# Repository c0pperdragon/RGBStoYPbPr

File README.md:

# RGBStoYPbPr

A fairly simple video converter from RGBS to YPbPr. My main challenge here is to make it work with only stuff that I have incidentially at home.
 
The PCB is a small single-sided leftover piece that was just big enough to fit the circuitry. Home etching, using the well-known toner transfer method,
turned out pretty nicely. To create the necessary non-standard resistor values, I soldered several resistors on top of each other. 
When allowing up to three resistors in a parallel configuration, the computer search finds an extremly good fit for every desired value
by using only the E6 series.

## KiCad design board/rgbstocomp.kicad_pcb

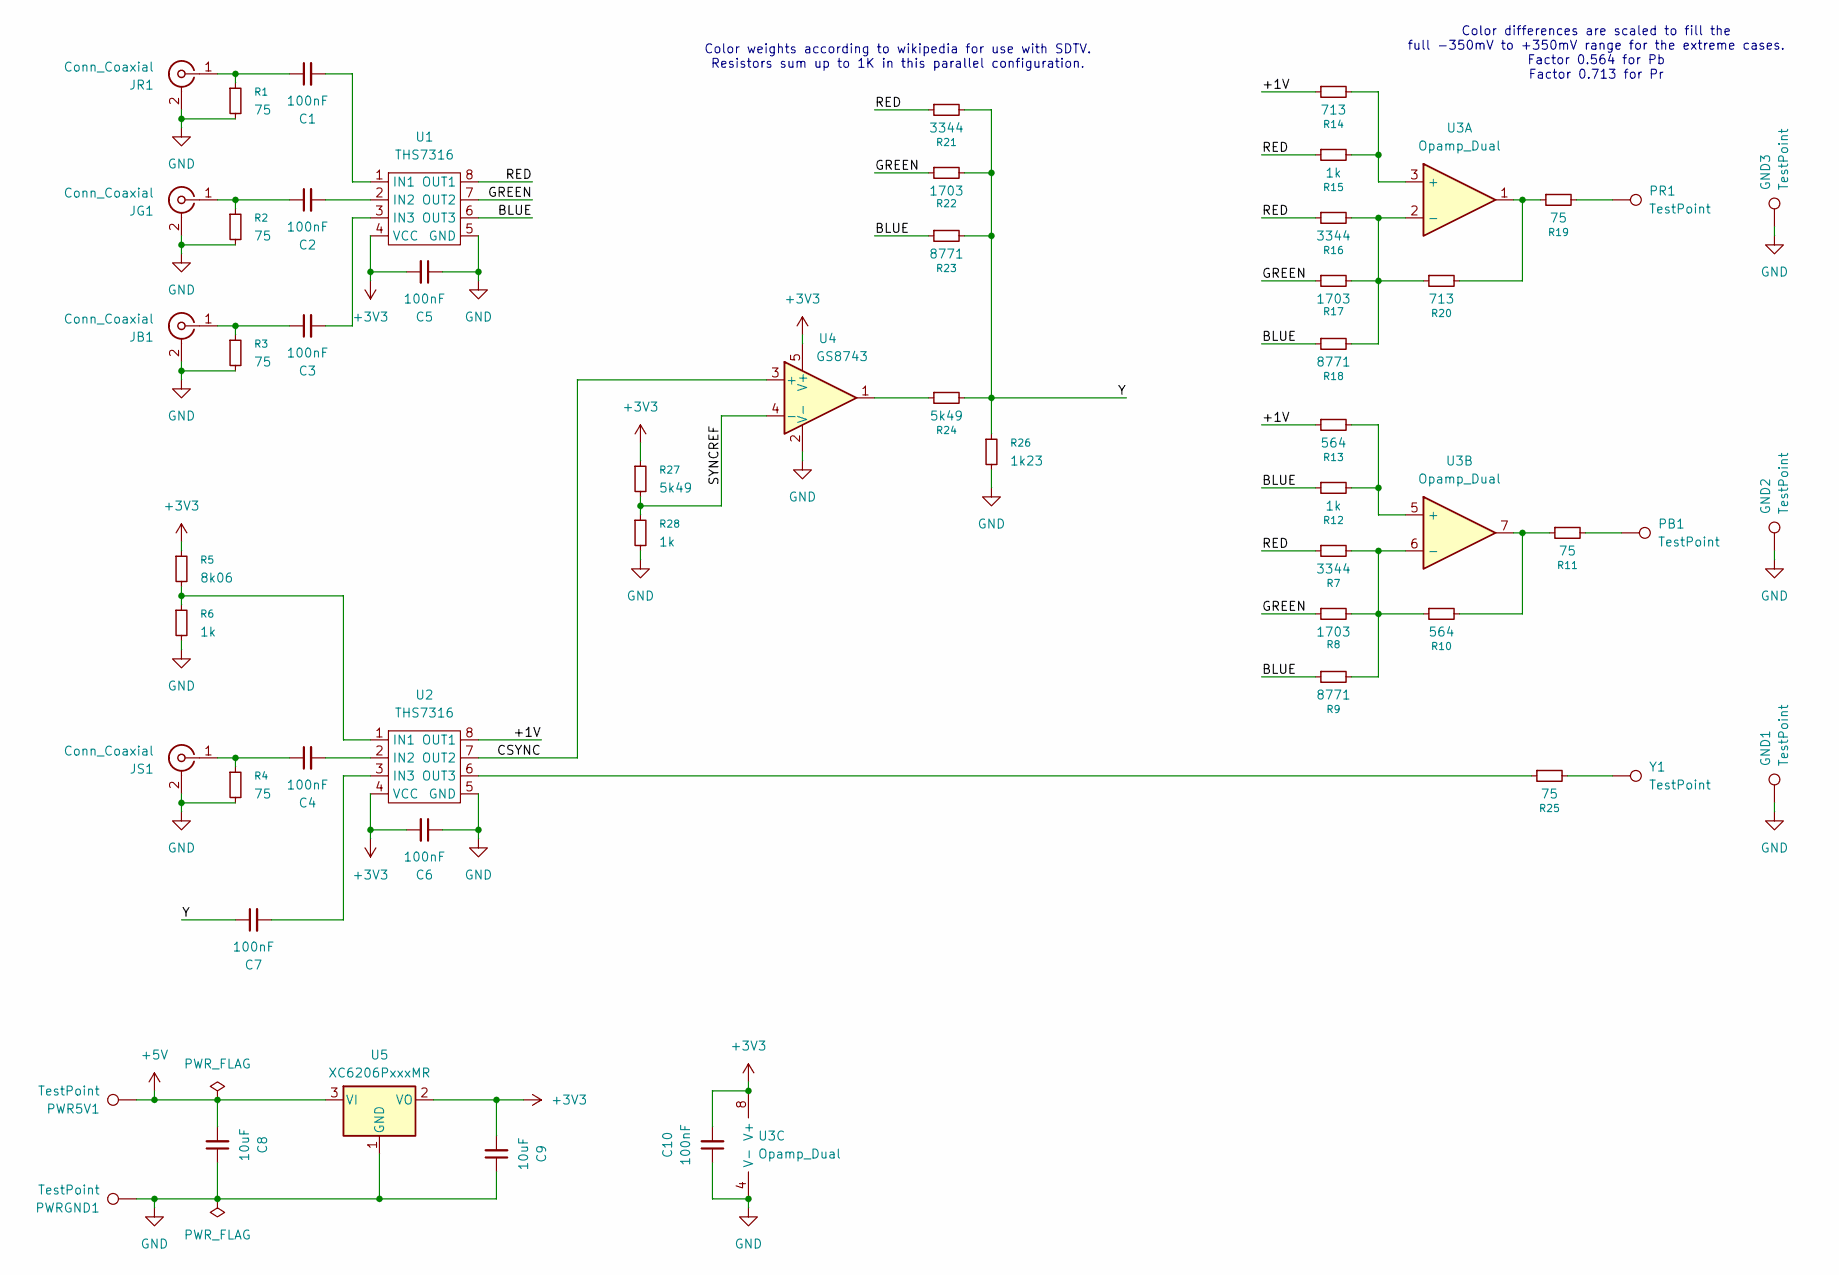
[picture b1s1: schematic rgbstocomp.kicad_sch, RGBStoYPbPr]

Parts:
C1, C2, C3, C4, C5, C6, C7, C10: 100nF; C_0805_2012Metric_Pad1.18x1.45mm_HandSolder
C8, C9: 10uF; C_0805_2012Metric_Pad1.18x1.45mm_HandSolder
GND1, GND2, GND3: TestPoint; TestPoint_Pad_3.0x3.0mm
JB1: Conn_Coaxial; 156-0097-E
JG1: Conn_Coaxial; 156-0097-E
JR1: Conn_Coaxial; 156-0097-E
JS1: Conn_Coaxial; 156-0097-E
PB1: TestPoint; TestPoint_Pad_3.0x3.0mm
PR1: TestPoint; TestPoint_Pad_3.0x3.0mm
PWR5V1: TestPoint; TestPoint_Pad_3.0x3.0mm
PWRGND1: TestPoint; TestPoint_Pad_3.0x3.0mm
R1, R2, R3, R4, R11, R19, R25: 75; R_0805_2012Metric_Pad1.20x1.40mm_HandSolder
R5: 8k06; R_0805_2012Metric_Pad1.20x1.40mm_HandSolder
R6, R12, R15, R28: 1k; R_0805_2012Metric_Pad1.20x1.40mm_HandSolder
R7, R16, R21: 3344; R_0805_2012Metric_Pad1.20x1.40mm_HandSolder
R8, R17, R22: 1703; R_0805_2012Metric_Pad1.20x1.40mm_HandSolder
R9, R18, R23: 8771; R_0805_2012Metric_Pad1.20x1.40mm_HandSolder
R10, R13: 564; R_0805_2012Metric_Pad1.20x1.40mm_HandSolder
R14, R20: 713; R_0805_2012Metric_Pad1.20x1.40mm_HandSolder
R24, R27: 5k49; R_0805_2012Metric_Pad1.20x1.40mm_HandSolder
R26: 1k23; R_0805_2012Metric_Pad1.20x1.40mm_HandSolder
U1, U2: THS7316; SO-8_3.9x4.9mm_P1.27mm
U3: Opamp_Dual; SO-8_3.9x4.9mm_P1.27mm
U4: GS8743; SOT-23-5
U5: XC6206PxxxMR; SOT-23-3
Y1: TestPoint; TestPoint_Pad_3.0x3.0mm

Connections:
+3V3: C5.2, C6.2, C9.2, C10.2, R5.1, R27.1, U1.4 (VCC), U2.4 (VCC), U3.8 (V+), U4.5 (V+), U5.2 (VO)
+5V: C8.2, PWR5V1.1, U5.3 (VI)
/+1V: R13.1, R14.1, U2.8 (OUT1)
/BLUE: R9.1, R12.1, R18.1, R23.1, U1.6 (OUT3)
/CSYNC: U2.7 (OUT2), U4.3 (+)
/GREEN: R8.1, R17.1, R22.1, U1.7 (OUT2)
/RED: R7.1, R15.1, R16.1, R21.1, U1.8 (OUT1)
/SYNCREF: R27.2, R28.1, U4.4 (-)
/Y: C7.1, R21.2, R22.2, R23.2, R24.2, R26.1
GND: C5.1, C6.1, C8.1, C9.1, C10.1, GND1.1, GND2.1, GND3.1, JB1.2 (Ext), JG1.2 (Ext), JR1.2 (Ext), JS1.2 (Ext), PWRGND1.1, R1.2, R2.2, R3.2, R4.2, R6.2, R26.2, R28.2, U1.5 (GND), U2.5 (GND), U3.4 (V-), U4.2 (V-), U5.1 (GND)
unnamed: C3.1, JB1.1 (In), R3.1
unnamed: C2.1, JG1.1 (In), R2.1
unnamed: C1.1, JR1.1 (In), R1.1
unnamed: C4.1, JS1.1 (In), R4.1
unnamed: PB1.1, R11.2
unnamed: PR1.1, R19.2
unnamed: R10.2, R11.1, U3.7
unnamed: R19.1, R20.2, U3.1
unnamed: R24.1, U4.1
unnamed: R25.2, Y1.1
unnamed: C1.2, U1.1 (IN1)
unnamed: C2.2, U1.2 (IN2)
unnamed: C3.2, U1.3 (IN3)
unnamed: R5.2, R6.1, U2.1 (IN1)
unnamed: C4.2, U2.2 (IN2)
unnamed: C7.2, U2.3 (IN3)
unnamed: R25.1, U2.6 (OUT3)
unnamed: R14.2, R15.2, U3.3 (+)
unnamed: R16.2, R17.2, R18.2, R20.1, U3.2 (-)
unnamed: R12.2, R13.2, U3.5 (+)
unnamed: R7.2, R8.2, R9.2, R10.1, U3.6 (-)

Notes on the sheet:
Color differences are scaled to fill the full -350mV to +350mV range for the extreme cases. Factor 0.564 for Pb Factor 0.713 for Pr
Color weights according to wikipedia for use with SDTV. Resistors sum up to 1K in this parallel configuration.

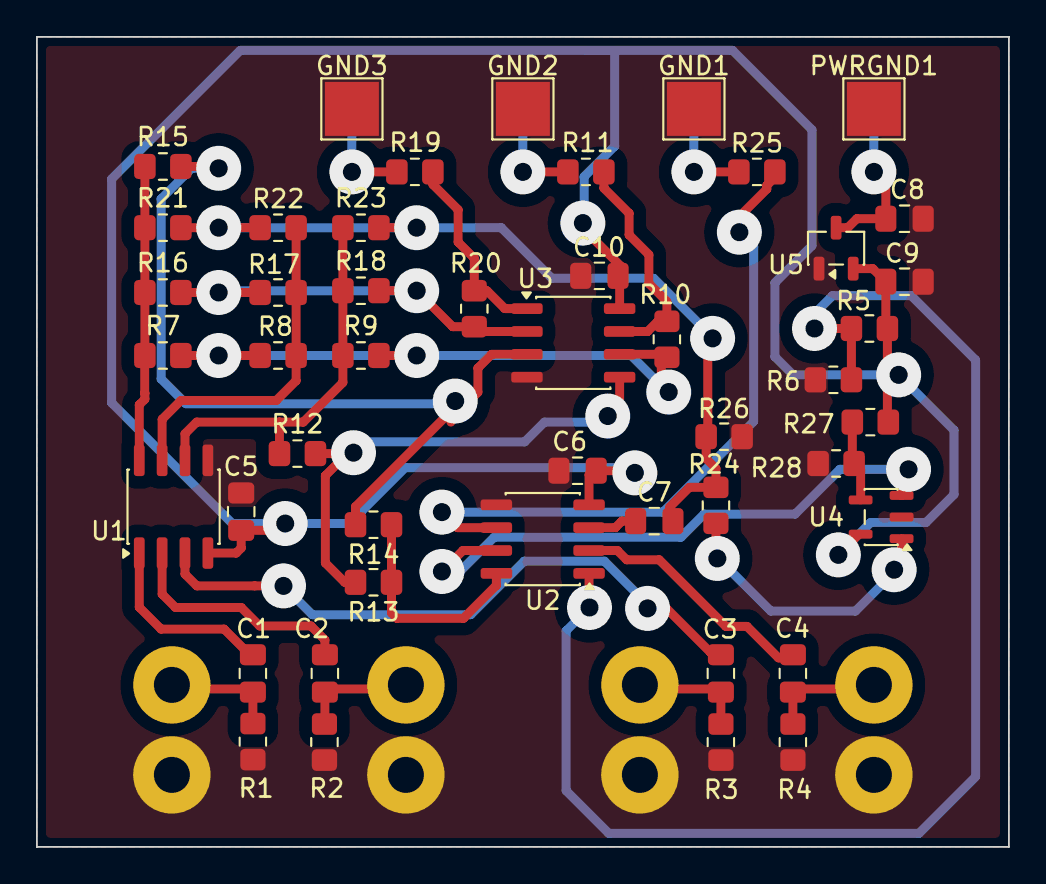
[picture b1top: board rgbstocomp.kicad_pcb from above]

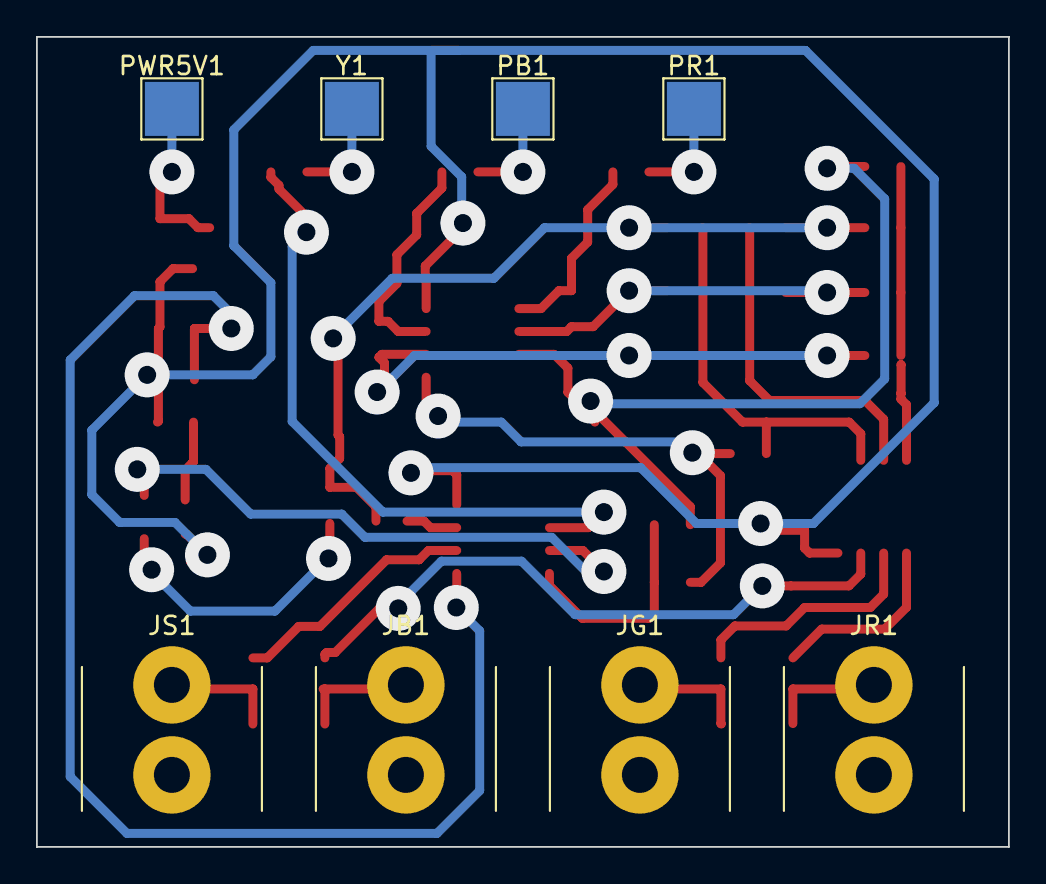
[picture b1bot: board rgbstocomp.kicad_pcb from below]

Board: 2 copper layers, 54.0 x 45.0 mm, 55 parts (8 on the bottom side), 31 nets.

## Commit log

2026-05-20 First schematic
2026-05-21 PCB design
2026-05-21 Fix CSYNC detection threashold
2026-05-24 Supply ICs with 3.3V instead of with 5V. Add documentation.
2026-05-24 Fix pic
2026-05-24 Change resistor to create the csync reference voltage
